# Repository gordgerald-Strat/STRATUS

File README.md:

# STRATUS
odular IoT hardware platform built around the dual-core **ESP32-D0WD-V3** SoC. Designed for high-reliability telemetry and edge computing, the system features a dedicated **Bosch BME688 4-in-1 gas sensor**, a **custom RF trace antenna**, **32MB high-speed flash storage**

*****FILES WILL BE UPLOAED ---- FINISHING UP*******

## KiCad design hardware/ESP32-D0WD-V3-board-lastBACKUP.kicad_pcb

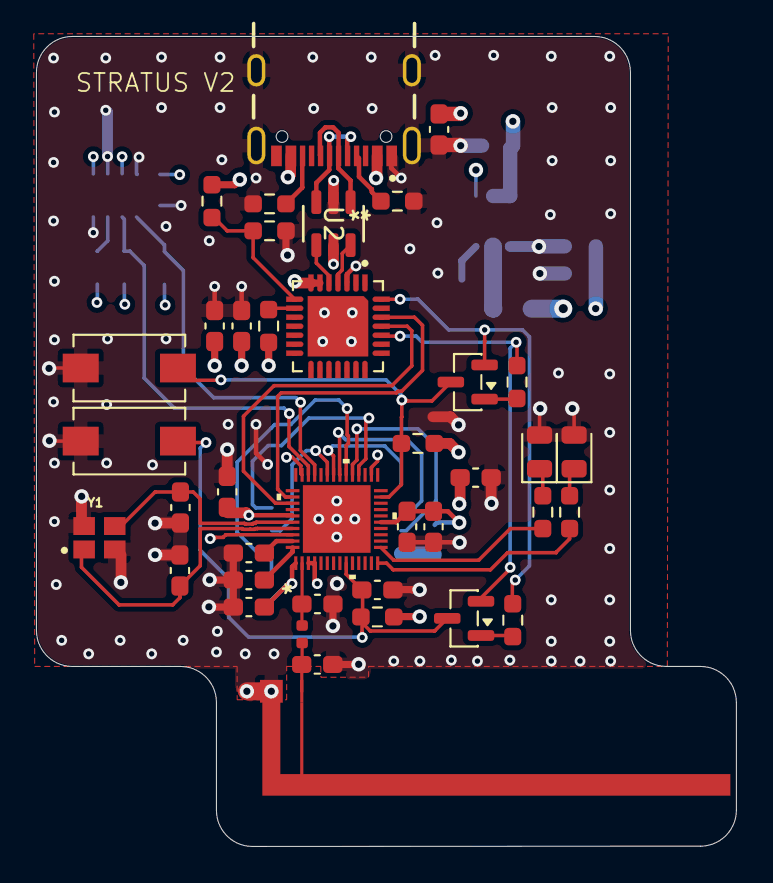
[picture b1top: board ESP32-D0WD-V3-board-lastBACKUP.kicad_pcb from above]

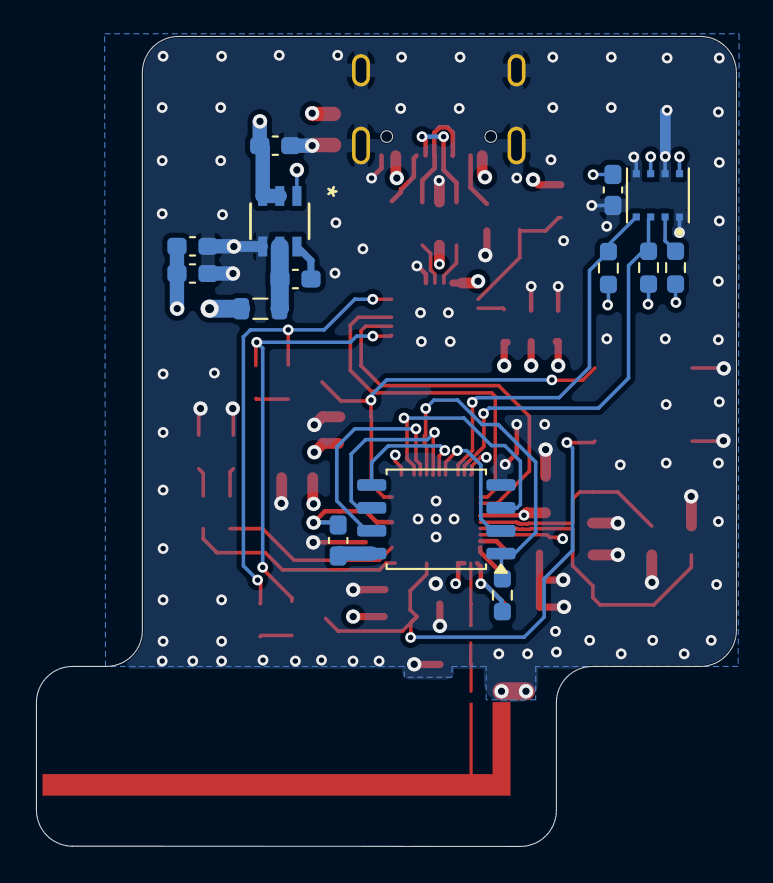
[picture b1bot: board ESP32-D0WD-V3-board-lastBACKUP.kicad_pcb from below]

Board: 4 copper layers, 38.9 x 45.0 mm, 53 parts (14 on the bottom side), 41 nets.

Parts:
C1, C7, C19: 4u7; C_0603_1608Metric_Pad1.08x0.95mm_HandSolder
C2, C3, C6, C8, C11, C14, C16, C17, C23, C24: 100n; C_0603_1608Metric_Pad1.08x0.95mm_HandSolder
C4, C5, C18, C25: 22u; C_0603_1608Metric_Pad1.08x0.95mm_HandSolder
C9, C10: 10p; C_0603_1608Metric_Pad1.08x0.95mm_HandSolder
C12: C_1p5; C_0603_1608Metric_Pad1.08x0.95mm_HandSolder
C13: C; C_0603_1608Metric_Pad1.08x0.95mm_HandSolder
D1, D2: RED; LED_0805_2012Metric
J1: USBC; GCT_USB4105-GF-A-120
L1: 4.7u; L_0805_2012Metric
L2: L_2n4; L_0402_1005Metric
Q2, Q3: SS8050; SOT-23
R1, R2, R9, R16: 5k1; R_0603_1608Metric_Pad0.98x0.95mm_HandSolder
R3, R5, R6, R7, R10, R11, R12, R13: 20k; R_0603_1608Metric_Pad0.98x0.95mm_HandSolder
R4: 47k; R_0603_1608Metric_Pad0.98x0.95mm_HandSolder
R14, R15: 330; R_0603_1608Metric_Pad0.98x0.95mm_HandSolder
SW1, SW2: SW_Push; SW_SPST_EVQPE1
U1: ESP32-D0WD-V3; QFN48_ESP32-D0WD-V3_EXP
U2: USB-PROT; TSOP-6_ONS-M
U3: BUCK_CONV; TSOT26_DIO-M
U4: USB-UART; IC_CP2102N-A02-GQFN28R
U5: Flash Memory; SOIC-8_5.3x5.3mm_P1.27mm
U6: BME688_SENSOR; IC_BME688
U7: Untitled
Y1: K3-CRYSTALL; XTAL_ECS-400-8-36Q-CWY-TR

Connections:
+3V3: C4.1, C5.1, C6.1, C7.1, C8.1, C11.2, C16.2, C17.1, C23.2, C24.2, C25.1, L1.2, R5.2, R6.1, R7.1, R9.1, R10.1, R11.1, R16.2, U1.1 (VDDA), U1.3 (VDD3P3), U1.4 (VDD3P3), U1.19 (VDD3P3_RTC), U1.26 (VDD_SDIO), U1.37 (VDD3P3_CPU), U1.43 (VDDA), U1.46 (VDDA), U3.1 (FB), U4.6 (VDD), U4.7 (VREGIN), U6.6 (VDDIO), U6.8 (VDD)
/BUCK_CONVERTOR/BOOT_STRAP: C3.1, U3.6 (BST)
/BUCK_CONVERTOR/FILTER: C3.2, L1.1, U3.5 (SW)
/LED_1: R14.1, U1.14 (GPIO25)
/LED_2: R15.1, U1.15 (GPIO26)
/USBC_INTERFACE/USBD+: J1.A6 (DP1), J1.B6 (DP2), U2.1
/USBC_INTERFACE/USBD-: J1.A7 (DN1), J1.B7 (DN2), U2.3
CS#-FLASH: R6.2, U1.30 (SD_CMD), U5.1 (CS#)
DTR-UART: Q2.2 (E), R13.1, U4.28 (DTR)
GND: C1.2, C2.2, C4.2, C5.2, C6.2, C7.2, C9.2, C10.2, C11.1, C12.2, C13.2, C14.2, C16.1, C17.2, C18.1, C19.2, C23.1, C24.1, C25.2, D1.2 (A), D2.2 (A), J1.A1_B12 (GND), J1.B1_A12 (GND__1), J1.SH1 (SHELL_GND), J1.SH2 (SHELL_GND__1), J1.SH3 (SHELL_GND__2), J1.SH4 (SHELL_GND__3), R1.2, R2.2, R3.1, SW1.1, SW2.1, U1.49 (GND), U2.2, U3.4 (GND), U4.3 (GND), U4.29 (EXP), U5.4 (GND), U6.1 (GND), U6.5 (SDO), U6.7 (GND__1), U7.2 (FEED), Y1.2 (GND), Y1.4 (GND__1)
LNA_RF: C12.1, L2.1, U1.2 (LNA_IN)
unnamed: D1.1 (K), R15.2
unnamed: D2.1 (K), R14.2
unnamed: J1.A5 (CC1), R1.1
unnamed: J1.B5 (CC2), R2.1
unnamed: Q2.1 (B), R12.2
unnamed: Q2.3 (C), R11.2, SW2.2, U1.23 (GPIO0)
unnamed: Q3.1 (B), R13.2
unnamed: C14.1, Q3.3 (C), R10.2, SW1.2, U1.9 (CHIP_PU)
unnamed: C2.1, U1.48 (CAP1)
unnamed: C1.1, U1.47 (CAP2)
unnamed: U2.6, U4.4 (D+)
unnamed: U2.4, U4.5 (D-)
unnamed: R3.2, R4.2, U4.8 (VBUS)
unnamed: R5.1, U4.9 (~RST)
unnamed: C8.2, U5.8 (VCC)
unnamed: R7.2, U6.2 (CSB)
unnamed: C13.1, L2.2, U7.1 (GND)
RTS-UART: Q3.2 (E), R12.1, U4.24 (RTS)
RXD-UART: U1.41 (U0TXD), U4.25 (RXD)
SCK-SENSOR: R9.2, U1.35 (GPIO18), U6.4 (SCK)
SCLK-FLASH: U1.31 (SD_CLK), U5.6 (SCLK)
SDI-SENSOR: R16.1, U1.36 (GPIO23), U6.3 (SDI)
SIO0-FLASH: U1.32 (SD_DATA_0), U5.5 (SI/SIO0)
SIO1-FLASH: U1.33 (SD_DATA_1), U5.2 (SI/SIO1)
SIO2-FLASH: U1.28 (SD_DATA_2), U5.3 (SIO2)
SIO3-FLASH: U1.29 (SD_DATA_3), U5.7 (SIO3)
TXD-UART: U1.40 (U0RXD), U4.26 (TXD)
VBUS: C18.2, C19.1, J1.A4_B9 (VBUS), J1.B4_A9 (VBUS__1), R4.1, U2.5, U3.2 (EN), U3.3 (VIN)
XTAL_1: C9.1, U1.45 (XTAL_P), Y1.1
XTAL_3: C10.1, U1.44 (XTAL_N), Y1.3
